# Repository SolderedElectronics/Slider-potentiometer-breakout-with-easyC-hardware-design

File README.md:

# Slider potentiometer breakout with easyC Hardware design

## About the product

|  |
| :----------------------------------------------------------: |
|      [Buy Slider potentiometer breakout with easyC](https://www.solde.red/333131)      |

Potentiometers are well known all around, and the sliding potentiometer is just one of its versions. You've probably seen it in some music equipment, and now you have the chance to add it to your project!

This board has easyC connector. Thanks to easyC ecosystem, this board can be connected using off-the-shelf cables, without soldering. Controlling the is as simple as it gets, too. Learn more about easyC here.

## Repository contents

All Soldered Electronics hardware designed in KiCAD, and repositories are organized in the following way:

- CAD folder - contains KiCAD files (Schematics, Board, Panel Board), sorted by version. Change log lists all changes between versions.
- OUTPUTS - contains useful files, such as Bill of Materials (BOM), PDF of schematics, 3D .step file of the board and gerber files, sorted by version. 
- OUTPUTS -> Compliance - Certificates and useful legal stuff. 

## Want to contribute?

Please feel free to submit a pull request if you have any contributions. We encourage you to submit an issue or pull request if you find a bug. 

## About Soldered

At Soldered, we design and manufacture a wide selection of electronic products to help you turn your ideas into acts and bring you one step closer to your final project. Our products are intented for makers and crafted in-house by our experienced team in Osijek, Croatia. We believe that sharing is a crucial element for improvement and innovation, and we work hard to stay connected with all our makers regardless of their skill or experience level. Therefore, all our products are open-source. Finally, we always have your back. If you face any problem concerning either your shopping experience or your electronics project, our team will help you deal with it, offering efficient customer service and cost-free technical support anytime. Some of those might be useful for you:

- [Web Store](https://www.soldered.com/shop)
- [Tutorials & Projects](https://soldered.com/learn)
- [Community & Technical support](https://soldered.com/community)

## License info

All Soldered open-source hardware (OSH) is under The TAPR Open Hardware License. Read more in the LICENSE file. 

No warranty - all designs in this repository are distributed in the hope that they will be useful, but without any warranty. They are provided "AS IS", therefore without warranty of any kind, either expressed or implied. The entire quality and performance of what you do with the contents of this repository are your responsibility. In no event, Soldered Electronics will be liable for your damages, losses, including any general, special, incidental or consequential damage arising out of the use or inability to use the contents of this repository. 

## Have fun! 
And thank you from your fellow makers at Soldered Electronics.

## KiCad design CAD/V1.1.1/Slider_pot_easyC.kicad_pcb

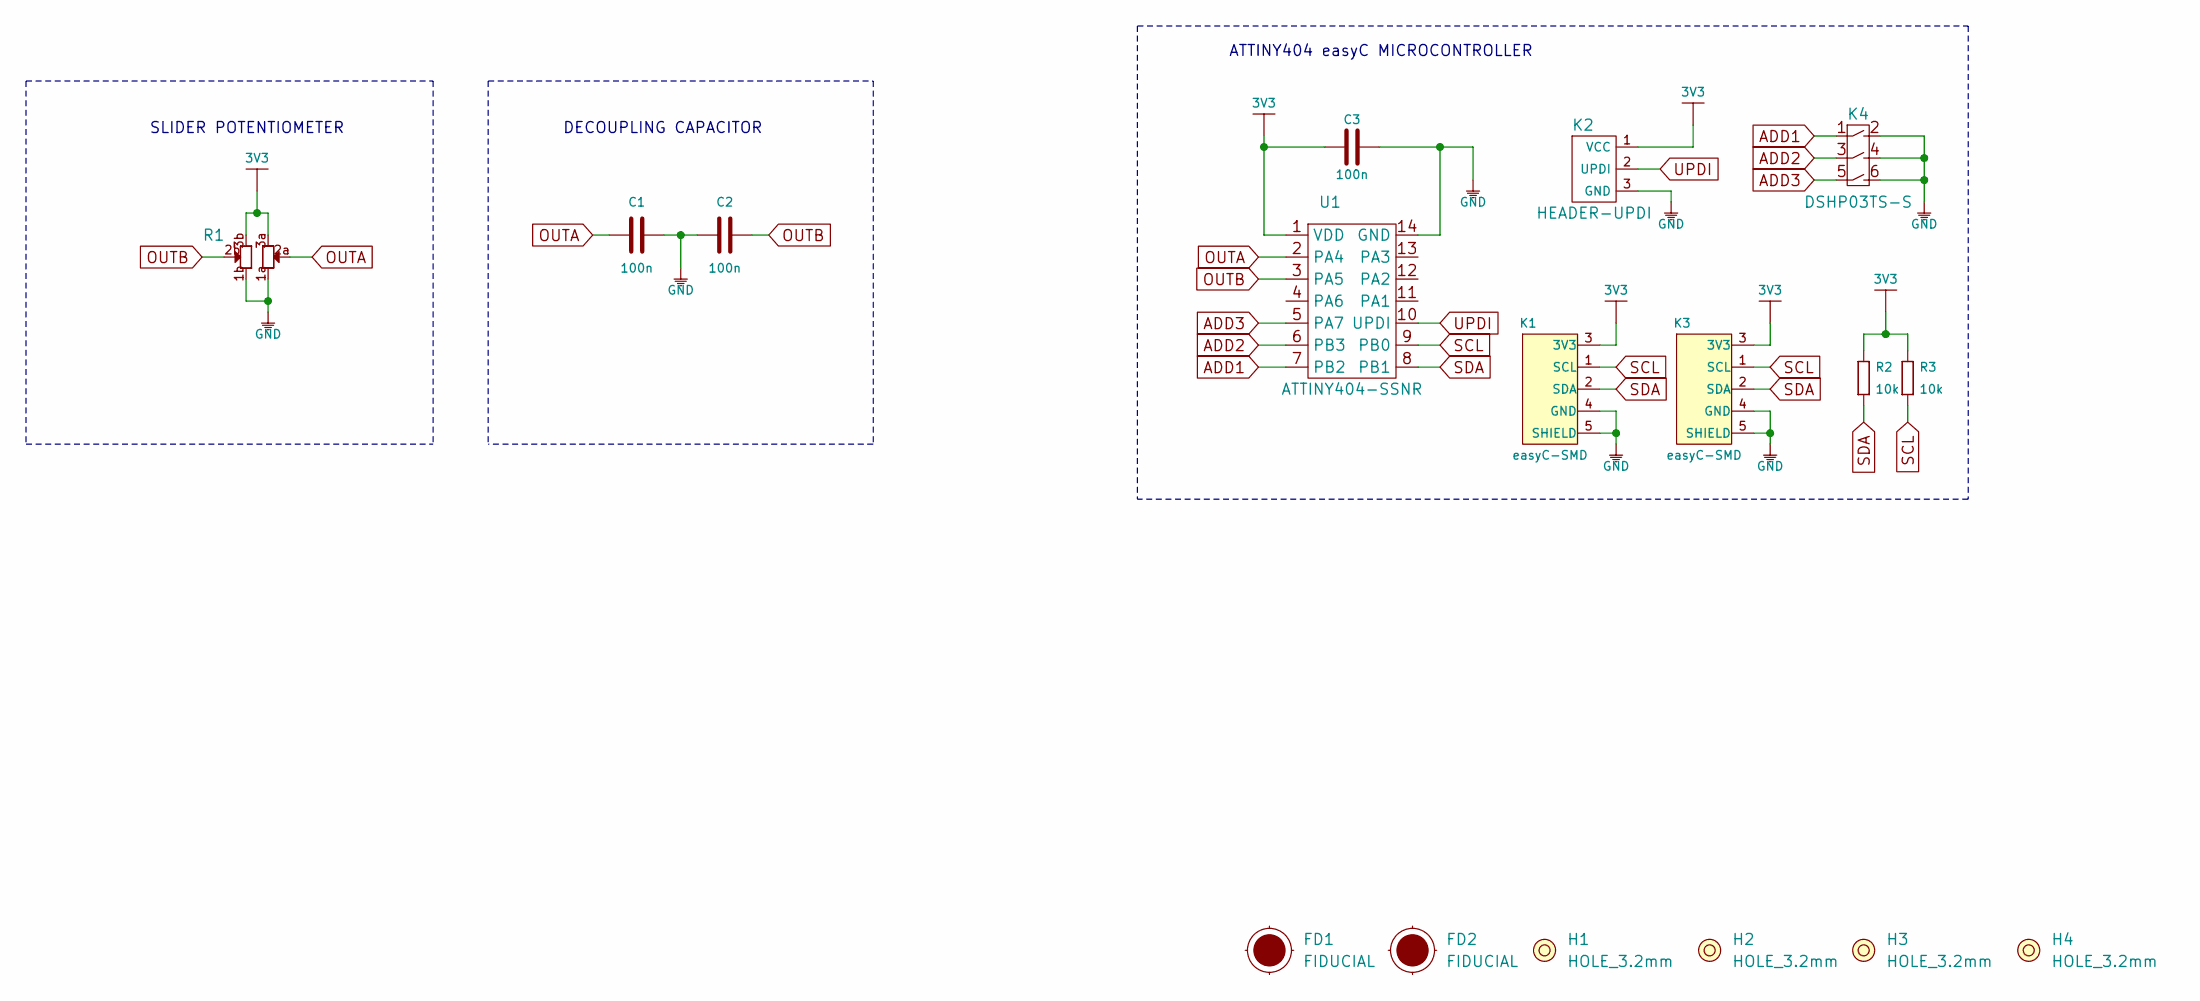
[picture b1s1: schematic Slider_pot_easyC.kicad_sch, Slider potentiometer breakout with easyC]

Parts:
C1, C2, C3: 100n; 0603C
FD1, FD2: FIDUCIAL; FIDUCIAL_23
H1, H2, H3, H4: HOLE_3.2mm
K1, K3: easyC-SMD; easyC-connector
K2: HEADER-UPDI
K4: DSHP03TS-S
R1: SLIDER_POT
R2, R3: 10k; 0603R
U1: ATTINY404-SSNR; SOIC-14

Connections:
3V3: C3.1, K1.3 (3V3), K2.1 (VCC), K3.3 (3V3), R1.3a, R1.3b, R2.2, R3.2, U1.1 (VDD)
ADD1: K4.1, U1.7 (PB2)
ADD2: K4.3, U1.6 (PB3)
ADD3: K4.5, U1.5 (PA7)
GND: C1.2, C2.1, C3.2, K1.4 (GND), K1.5 (SHIELD), K2.3 (GND), K3.4 (GND), K3.5 (SHIELD), K4.2, K4.4, K4.6, R1.1a, R1.1b, U1.14 (GND)
OUTA: C1.1, R1.2a, U1.2 (PA4)
OUTB: C2.2, R1.2b, U1.3 (PA5)
SCL: K1.1 (SCL), K3.1 (SCL), R3.1, U1.9 (PB0)
SDA: K1.2 (SDA), K3.2 (SDA), R2.1, U1.8 (PB1)
UPDI: K2.2 (UPDI), U1.10 (UPDI)

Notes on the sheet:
SLIDER POTENTIOMETER
ATTINY404 easyC MICROCONTROLLER
DECOUPLING CAPACITOR

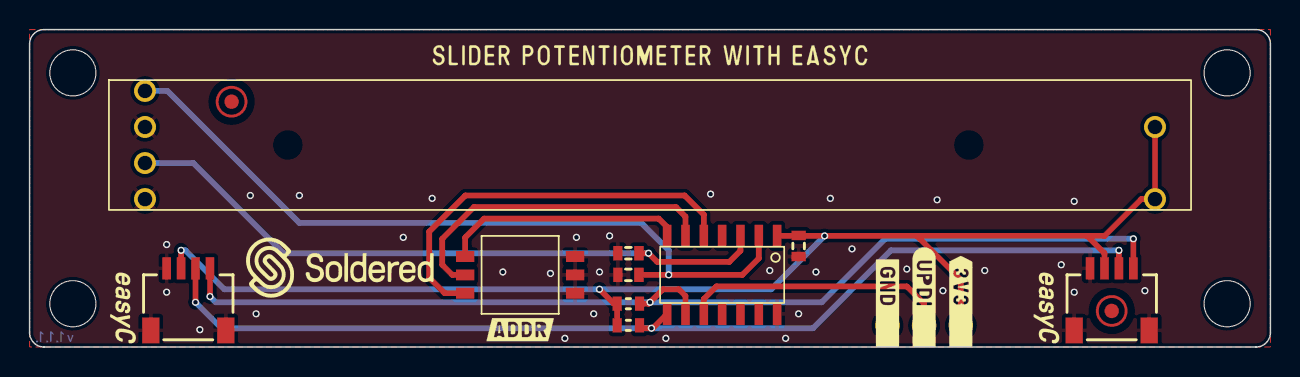
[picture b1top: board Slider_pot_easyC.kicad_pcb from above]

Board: 2 copper layers, 86.0 x 22.0 mm, 17 parts (0 on the bottom side), 10 nets.

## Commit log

2022-08-06 Updating open source files.
